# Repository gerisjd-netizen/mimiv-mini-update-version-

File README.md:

# MIMIC Mini - IR Cloner

MIMIC Mini is a compact infrared (IR) cloner and universal remote device. It is capable of reliably transmitting IR signals at ranges of up to 10–15 meters. It is fully compatible with Flipper Zero `.ir` files and provides up to 3 days of battery life under normal usage. Equipped with microSD card storage and an integrated receiver unit, it can record and save captured signals in both raw `.txt` and standard `.ir` formats.

---

## 🛠 Features

* **Extended Range:** Transmits IR signals up to 10–15 meters.
* **Flipper Zero Compatibility:** Natively supports `.ir` signal files.
* **Long Battery Life:** Up to 3 days of standard operational time.
* **Expandable Storage:** MicroSD card support for storing large databases of IR codes.
* **Signal Capture:** Built-in receiver capable of capturing and saving raw TXT or structured IR formats.

---

## 🏗 Housing & Assembly Instructions

1. **Belt Clip Attachment:**
   * The bill of materials (BOM) does not include the 3mm press-fit brass inserts or corresponding screws. 
   * The belt clip mount should be glued directly to the back of the enclosure for easy belt attachment.

2. **Display Insulation (CRITICAL):**
   * Before inserting the display, **apply insulating adhesive tape (e.g., Kapton or electrical tape) to the back of the display board**.
   * *Warning:* Failure to insulate the back of the display may cause a short circuit against the MicroSD card socket.

3. **IR LED Alignment:**
   * Pay close attention to the positioning and angles of the IR LEDs. 
   * If all LEDs are pointing straight forward, the transmission beam spread will be reduced, making it harder to aim at target devices. Angle them slightly outward to maximize signal coverage.

4. **Battery & Power Switch Wiring:**
   * Solder the battery directly to the `BAT` pads on the bottom of the ESP32-C3 board.
   * Wire the power switch in series with the positive battery lead to break the circuit.
   * Glue the power switch to the side of the PCB as demonstrated in the assembly photos.

---

## 📁 SD Card Structure & Usage

Upon inserting an SD card for the first time, the device will automatically generate three directories:
### 1. `saved_ir/`
* Captured IR signals are saved here. You can set the target capture format (`.ir` or `.txt`) in the device settings menu.
* Files in this folder can be renamed freely.
* If you place a multi-code `.ir` file in this folder, opening it on the device will display a sub-menu containing each individual code, allowing you to trigger them selectively one by one.

### 2. `universal/`
* If a multi-code `.ir` file is placed in the `universal` directory, the device will sequentially play back **all** IR codes inside the file one after another (e.g., universal power-off sequence). You will not be able to select individual codes in this mode.

---

## ⚙️ Settings

* **Transmitter Selection:** Through the system settings, you can toggle between using the internal IR transmitter array or an external IR module/emitter.

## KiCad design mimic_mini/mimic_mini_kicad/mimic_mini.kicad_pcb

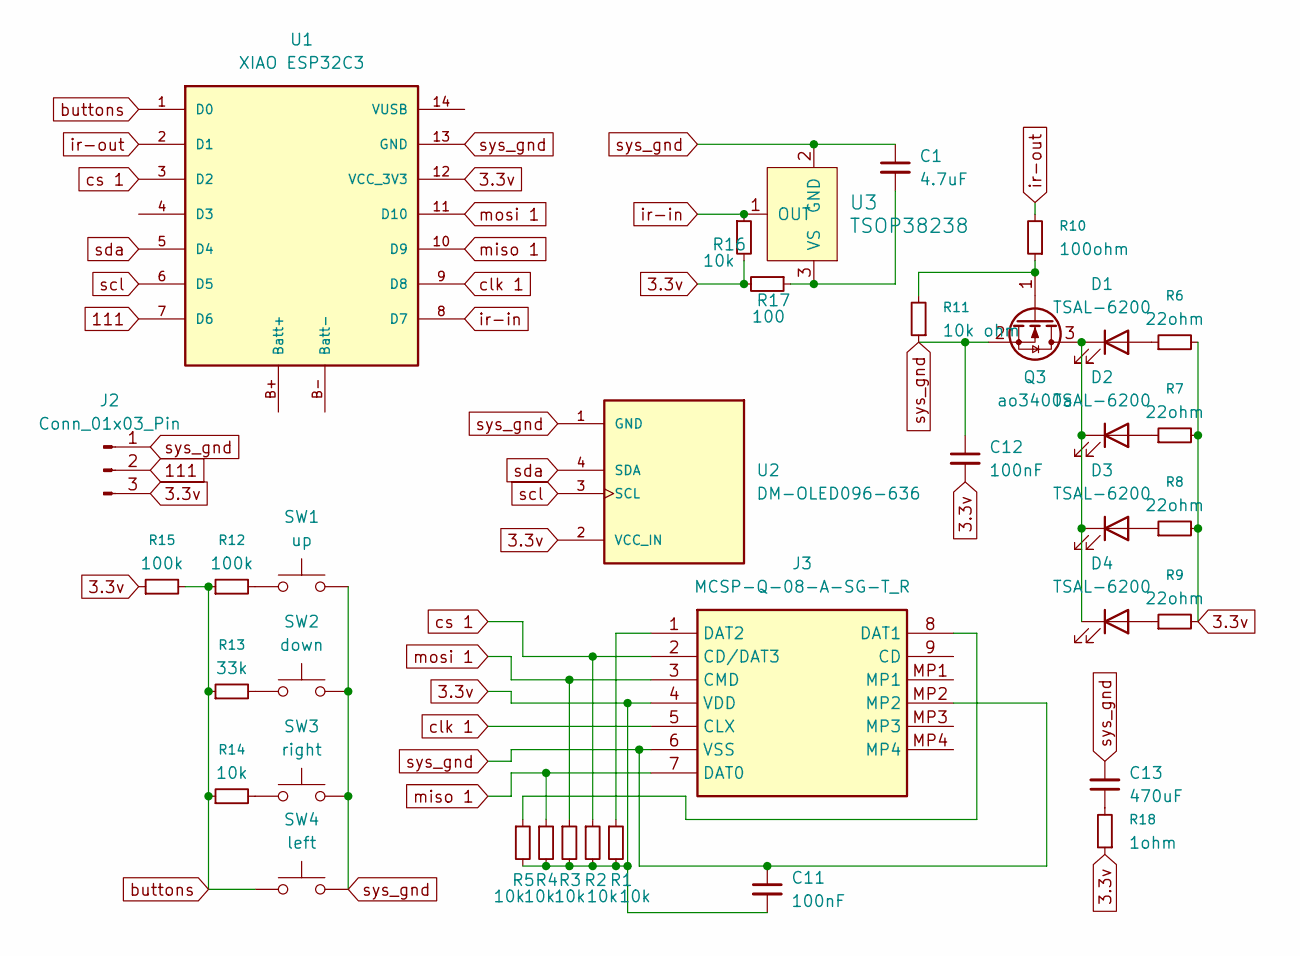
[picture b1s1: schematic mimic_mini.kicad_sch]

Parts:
C1: 4.7uF; C_0805_2012Metric
C11, C12: 100nF; C_0805_2012Metric
C13: 470uF; CP_Radial_D10.0mm_P3.80mm
D1, D2, D3, D4: TSAL-6200; LED_D5.0mm
J2: Conn_01x03_Pin; PinHeader_1x03_P2.54mm_Vertical
J3: MCSP-Q-08-A-SG-T_R; MCSPQ08ASGTR; Manufacturer_Part_Number MCSP-Q-08-A-SG-T/R
Q3: ao3400a; SOT-23
R1, R2, R3, R4, R5, R14, R16: 10k; R_0805_2012Metric_Pad1.20x1.40mm_HandSolder
R6, R7, R8, R9: 22ohm; R_0805_2012Metric_Pad1.20x1.40mm_HandSolder
R10: 100ohm; R_0805_2012Metric_Pad1.20x1.40mm_HandSolder
R11: 10k ohm; R_0805_2012Metric_Pad1.20x1.40mm_HandSolder
R12, R15: 100k; R_0805_2012Metric_Pad1.20x1.40mm_HandSolder
R13: 33k; R_0805_2012Metric_Pad1.20x1.40mm_HandSolder
R17: 100; R_0805_2012Metric_Pad1.20x1.40mm_HandSolder
R18: 1ohm; R_0805_2012Metric_Pad1.20x1.40mm_HandSolder
SW1: up; SW_PUSH_6mm
SW2: down; SW_PUSH_6mm
SW3: right; SW_PUSH_6mm
SW4: left; SW_PUSH_6mm
U1: XIAO ESP32C3; XIAO-ESP32-C3-DIP-SMD
U2: DM-OLED096-636; MODULE_DM-OLED096-636; PARTREV 2018-09-10
U3: TSOP38238; Vishay_MINICAST-3Pin; MPN TSOP38238; Digi-Key_PN 751-1227-ND

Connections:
3.3v: C11.2, C12.2, J2.3, J3.4 (VDD), R1.2, R2.2, R3.2, R4.2, R5.2, R6.2, R7.2, R8.2, R9.2, R15.1, R16.2, R17.2, R18.1, U1.12 (VCC_3V3), U2.2 (VCC_IN)
111: J2.2, U1.7 (D6)
unnamed: C13.1, R18.2
unnamed: D1.2 (A), R6.1
unnamed: D1.1 (K), D2.1 (K), D3.1 (K), D4.1 (K), Q3.3 (D)
unnamed: D2.2 (A), R7.1
unnamed: D3.2 (A), R8.1
unnamed: D4.2 (A), R9.1
unnamed: J3.8 (DAT1), R5.1
unnamed: J3.1 (DAT2), R1.1
unnamed: Q3.1 (G), R10.1, R11.2
unnamed: R12.2, SW1.1
unnamed: R13.2, SW2.1
unnamed: R14.2, SW3.1
unnamed: C1.2, R17.1, U3.3 (VS)
buttons: R12.1, R13.1, R14.1, R15.2, SW4.1, U1.1 (D0)
clk 1: J3.5 (CLX), U1.9 (D8)
cs 1: J3.2 (CD/DAT3), R2.1, U1.3 (D2)
ir-in: R16.1, U1.8 (D7), U3.1 (OUT)
ir-out: R10.2, U1.2 (D1)
miso 1: J3.7 (DAT0), R4.1, U1.10 (D9)
mosi 1: J3.3 (CMD), R3.1, U1.11 (D10)
scl: U1.6 (D5), U2.3 (SCL)
sda: U1.5 (D4), U2.4 (SDA)
sys_gnd: C1.1, C11.1, C12.1, C13.2, J2.1, J3.6 (VSS), J3.MP2, Q3.2 (S), R11.1, SW1.2, SW2.2, SW3.2, SW4.2, U1.13 (GND), U2.1 (GND), U3.2 (GND)

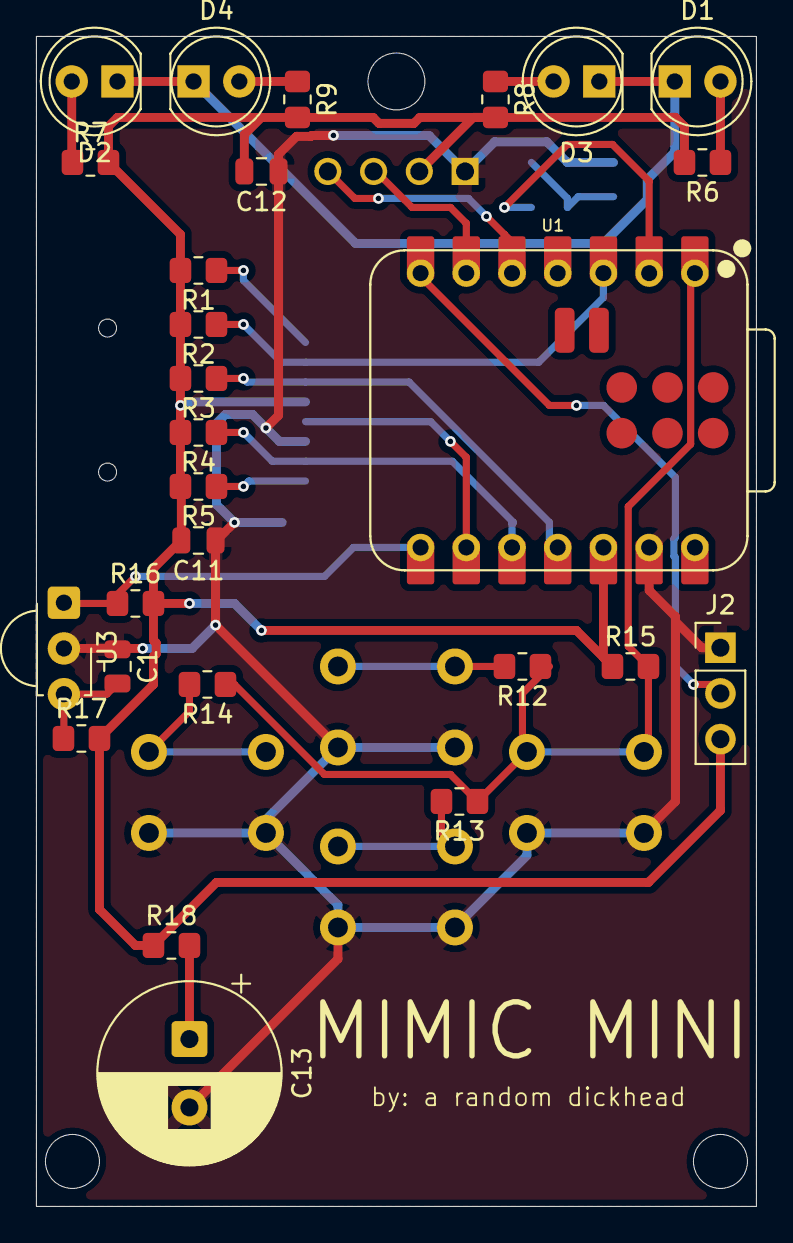
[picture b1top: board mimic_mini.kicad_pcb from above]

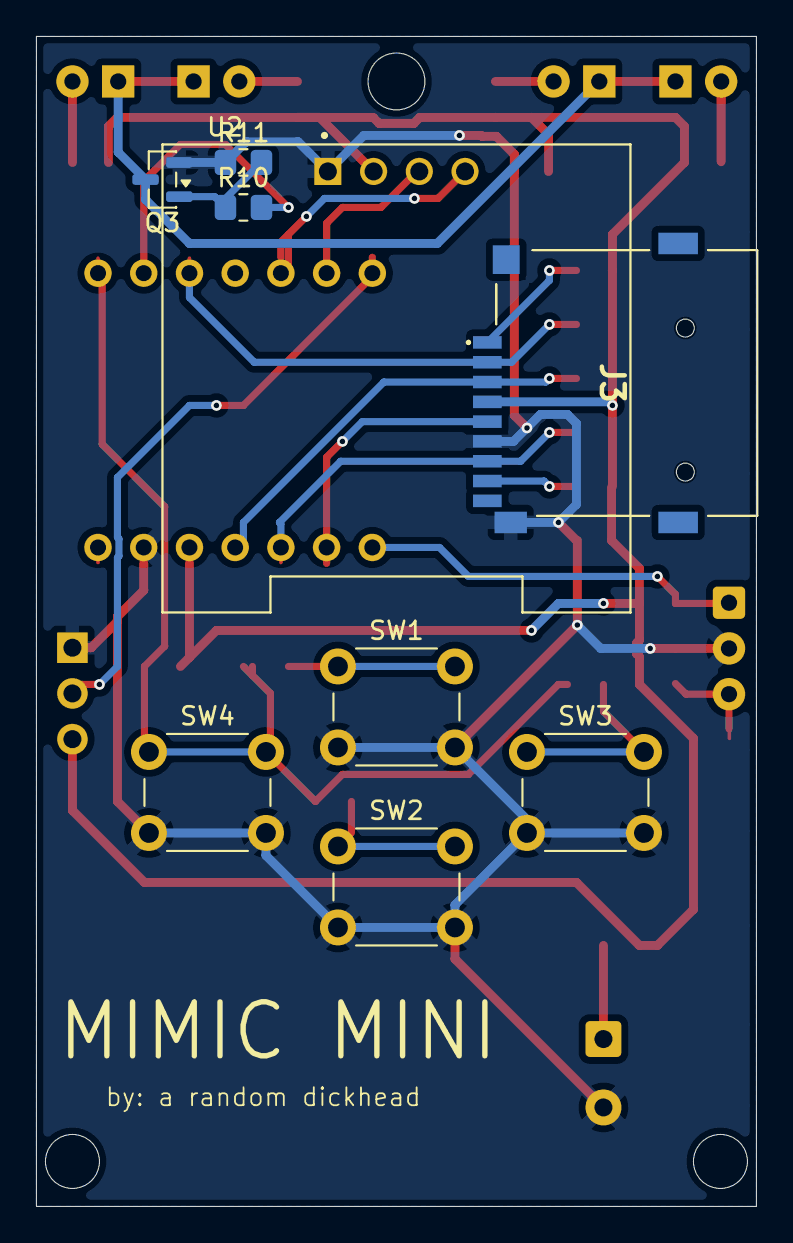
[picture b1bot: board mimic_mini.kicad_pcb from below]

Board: 2 copper layers, 40.0 x 65.0 mm, 36 parts (9 on the bottom side), 25 nets.
